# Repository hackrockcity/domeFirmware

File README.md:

domeFirmware
============

LED driver for the dome project. Each board can control 8 LED strips, each of which is up to 5m long.

## python_host
A python server that listens on UDP for a serialized 24bit RGB stream (8 bits per channel) that describes a 24 wide by 160 high image from top left to bottom right. (Yo dawg your aspect ratio is wrong). The data is then output to a Teensy over a high-speed serial port.

Usage:

```python
    python domelistener.py
```

## board
PCB design for the breakout board

## firmware
Firmware that should be compiled using the Makefile, then uploaded to the teensy using the teensy utility.

## mounting hardware
3d models for whatever mounts.

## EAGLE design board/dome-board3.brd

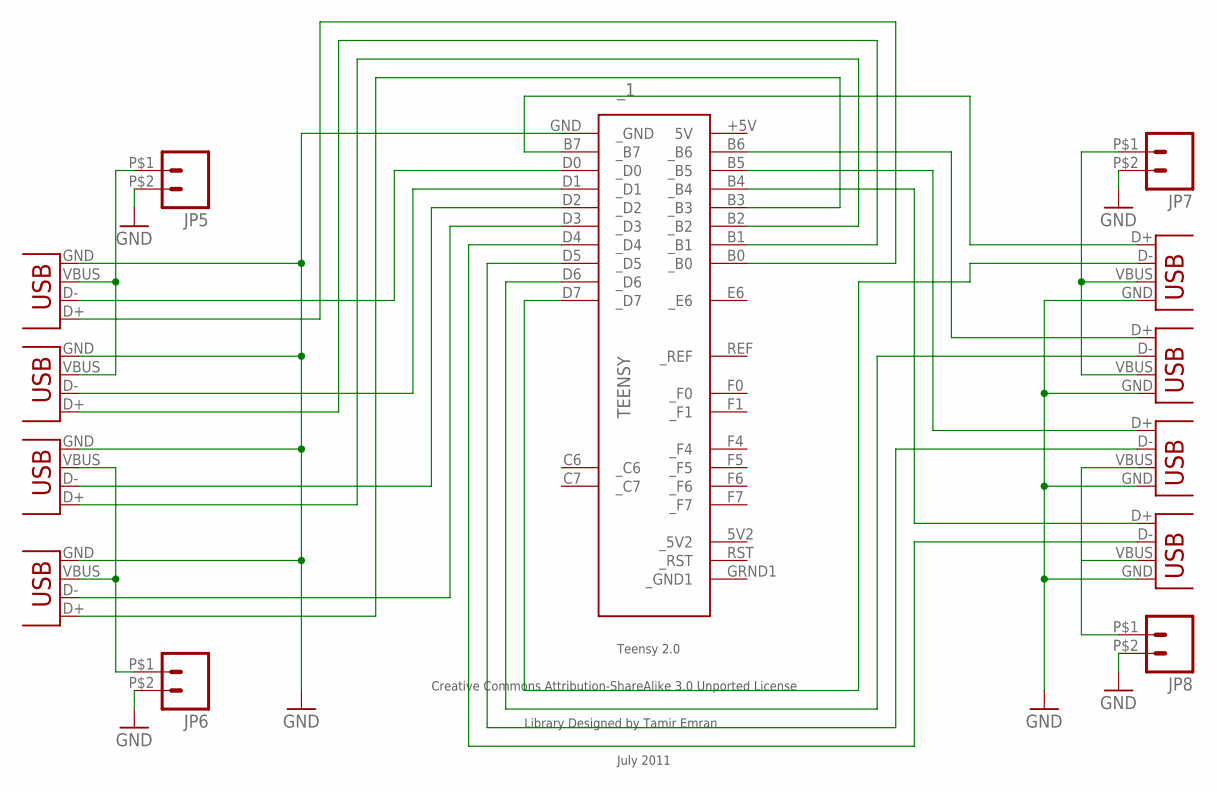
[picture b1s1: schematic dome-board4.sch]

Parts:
JP5, JP6, JP7, JP8: M026.35MM; SCREWTERMINAL-6.35MM-2
USB1, USB2, USB3, USB4, USB5, USB6, USB7, USB8: USB; USBA
_1: TEENSY

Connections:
GND: JP5.P$2 (2), JP6.P$2 (2), JP7.P$2 (2), JP8.P$2 (2), USB1.GND, USB2.GND, USB3.GND, USB4.GND, USB5.GND, USB6.GND, USB7.GND, USB8.GND, _1.GND (_GND)
unnamed: USB1.D+, _1.B0 (_B0)
unnamed: USB2.D+, _1.B1 (_B1)
unnamed: USB3.D+, _1.B2 (_B2)
unnamed: USB4.D+, _1.B3 (_B3)
unnamed: USB5.D+, _1.B4 (_B4)
unnamed: USB6.D+, _1.B5 (_B5)
unnamed: USB7.D+, _1.B6 (_B6)
unnamed: USB1.D-, _1.D0 (_D0)
unnamed: USB2.D-, _1.D1 (_D1)
unnamed: USB3.D-, _1.D2 (_D2)
unnamed: USB4.D-, _1.D3 (_D3)
unnamed: USB5.D-, _1.D4 (_D4)
unnamed: USB6.D-, _1.D5 (_D5)
unnamed: USB7.D-, _1.D6 (_D6)
unnamed: USB8.D-, _1.D7 (_D7)
unnamed: USB8.D+, _1.B7 (_B7)
VCC1: JP5.P$1 (1), USB1.VBUS, USB2.VBUS
VCC2: JP7.P$1 (1), USB7.VBUS, USB8.VBUS
VCC3: JP6.P$1 (1), USB3.VBUS, USB4.VBUS
VCC4: JP8.P$1 (1), USB5.VBUS, USB6.VBUS

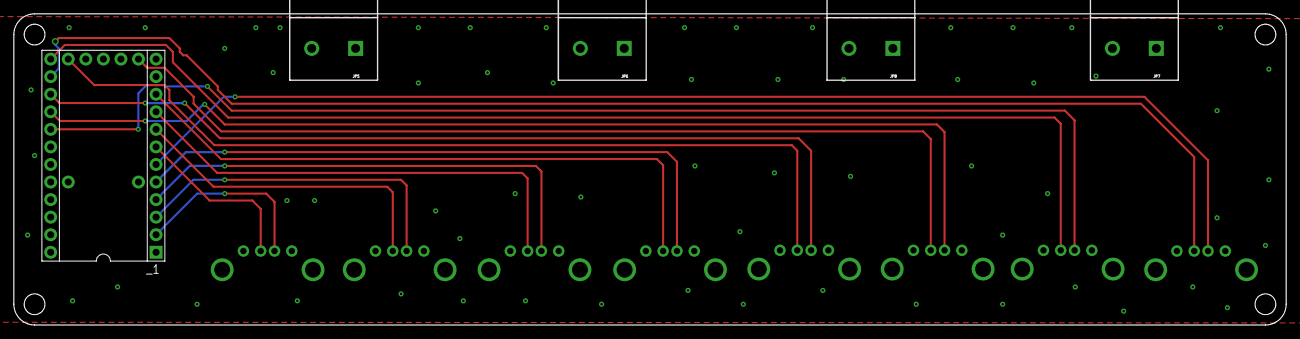
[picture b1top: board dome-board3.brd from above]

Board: 2 copper layers, 184.0 x 45.0 mm, 13 parts (0 on the bottom side), 21 nets.

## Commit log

2012-04-29 added host
2012-04-29 adding teensy firmware and dependencies
2012-04-30 updated readme with host spec
2012-05-01 initial driver boards
2012-05-01 adding dome-board 2 and 3
2012-05-02 updated dome-board3
2012-05-02 Break the controller out into a class.
2012-05-02 Woo! Can control!
2012-05-02 Re-organize files.
2012-05-03 updated circuit board
2012-05-03 cleaned up firmware
2012-05-03 Updated makefile to reference firmware.c
2012-05-03 Rainbows and dreams and ponys and 25fps with three teensies on an i7.
2012-05-03 some attempt at multithreading.
2012-05-03 adding enclosures file
2012-05-08 final board
2012-05-11 Bump for new strip geometry.
2012-05-12 FIX ALL THE ERRORS
2012-05-12 Drop frames so as not to fall behind.
2012-05-18 use multithreading. almost works.
2012-05-18 Something like ~28fps for 3 channels on a MacBook Pro
2012-05-18 Add board standoff model
2012-05-18 fix unit test.
2012-05-18 Make udp listener fast, still need to fix data formatter.
2012-05-18 bugfix.
2012-05-18 Slightly faster...
2012-05-23 First pass at a C++ host, because i don't know how to make Python faster.
2012-05-24 verking?
2012-05-24 Woo! Serial send works!
2012-05-24 Matt: update cpp host so it works with modern compilers.
2012-05-24 Update c++ host to work with modern compilers.
2012-05-25 Single port version of a c++ UDP listener.
2012-05-25 Works on linux, spits characters randomly on os x.
2012-05-25 bugfix: must initialize all added strips.
2012-05-25 Add coreldraw file for the bar mounts
2012-05-26 Appears to be mappped correctly, finally.
2012-06-24 getting rid of unterminated if?
2012-06-28 Add command line options to the c++ host.
2012-06-28 Fix usb ids
2012-06-29 Add threading; each strip gets updated in its own pthread. This is somehow more jittery than the round-robin version, perhaps devices are blocking.
2012-06-29 firmware: removed unused code.
2012-06-29 move python host.
2012-06-29 nonworking threading (segfault)
2012-06-29 can work?
2012-07-01 example launch script for linux.
2012-10-27 Add the f***ing executible.
2013-03-25 Adding UDP timeshifting script
2015-05-04 Manual for the uninitiated
2015-08-02 Domestar lives again???
2015-08-03 Dome board Rev4
2015-08-03 New board, as ordered
2015-08-07 Update firmware to work with modern avr-gcc

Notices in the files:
parts and their libraries:
teensy: Licensed Under Creative Commons
teensy: Creative Commons Attribution-ShareAlike 3.0 Unported License
teensy: Licensed Under Creative Commons Attribution-ShareAlike 3.0 Unported (CC BY-SA 3.0)
